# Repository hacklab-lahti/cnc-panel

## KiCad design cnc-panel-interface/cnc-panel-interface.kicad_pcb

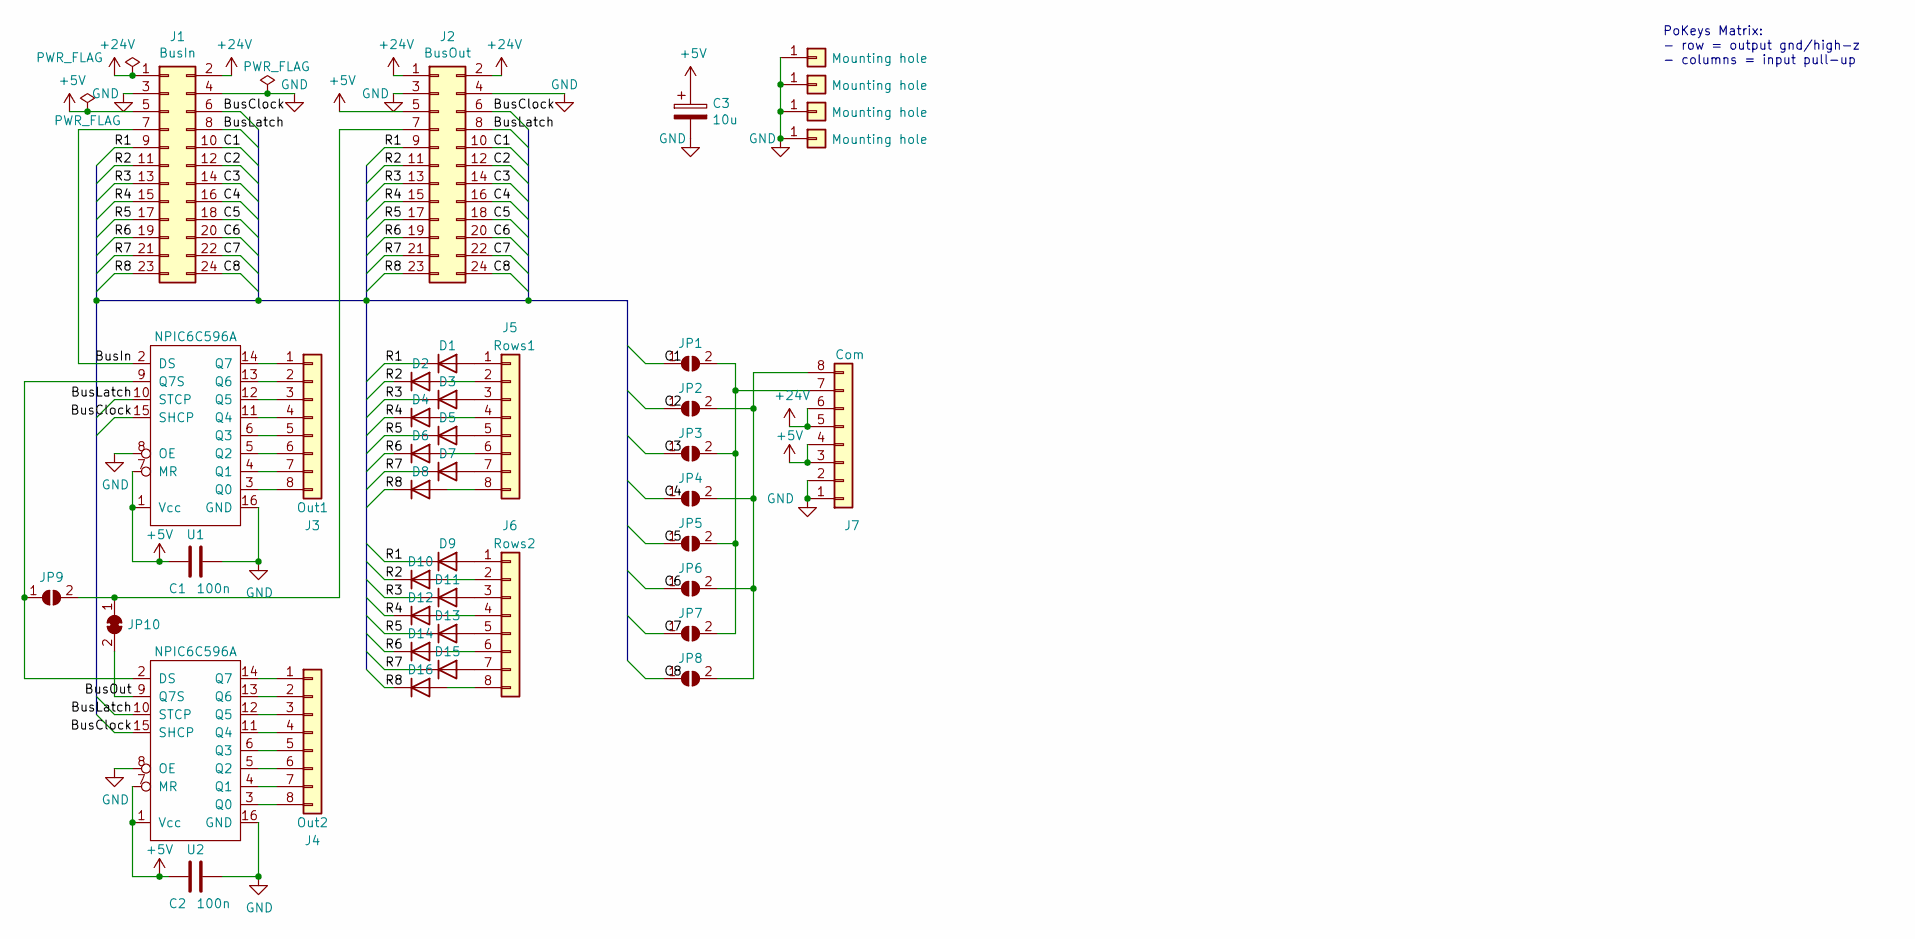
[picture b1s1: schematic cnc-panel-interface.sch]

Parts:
C1, C2: 100n; C_0805_2012Metric_Pad1.15x1.40mm_HandSolder
C3: 10u; CP_Elec_4x4.5
D1, D2, D3, D4, D5, D6, D7, D8, D9, D10, D11, D12, D13, D14, D15, D16: 1N4148; D_SOD-123
J1: BusIn; IDC-Header_2x12_P2.54mm_Vertical_2
J2: BusOut; IDC-Header_2x12_P2.54mm_Vertical_2
J3: Out1; Phoenix1989803
J4: Out2; Phoenix1989803
J5: Rows1; Phoenix1989803
J6: Rows2; Phoenix1989803
J7: Com; Phoenix1989803
J8, J9, J10, J11: Mounting hole; MountingHole_3.2mm_M3_Pad
JP1, JP2, JP3, JP4, JP5, JP6, JP7, JP8, JP9: SolderJumper_2_Open; SolderJumper-2_P1.3mm_Open_RoundedPad1.0x1.5mm
JP10: SolderJumper_2_Bridged; SolderJumper-2_P1.3mm_Bridged_RoundedPad1.0x1.5mm
U1, U2: NPIC6C596A; SOIC-16_3.9x9.9mm_P1.27mm

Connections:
+5V: C1.1, C2.1, C3.1, J1.5, J2.5, J7.3, J7.4, U1.1 (Vcc), U1.7 (MR), U2.1 (Vcc), U2.7 (MR)
+24V: J1.1, J1.2, J2.1, J2.2, J7.5, J7.6
/BusClock: J1.6, J2.6, U1.15 (SHCP), U2.15 (SHCP)
/BusIn: J1.7, U1.2 (DS)
/BusLatch: J1.8, J2.8, U1.10 (STCP), U2.10 (STCP)
/BusOut: JP10.2 (B), U2.9 (Q7S)
/C1: J1.10, J2.10, JP1.1 (A)
/C2: J1.12, J2.12, JP2.1 (A)
/C3: J1.14, J2.14, JP3.1 (A)
/C4: J1.16, J2.16, JP4.1 (A)
/C5: J1.18, J2.18, JP5.1 (A)
/C6: J1.20, J2.20, JP6.1 (A)
/C7: J1.22, J2.22, JP7.1 (A)
/C8: J1.24, J2.24, JP8.1 (A)
/R1: D1.1 (K), D9.1 (K), J1.9, J2.9
/R2: D2.1 (K), D10.1 (K), J1.11, J2.11
/R3: D3.1 (K), D11.1 (K), J1.13, J2.13
/R4: D4.1 (K), D12.1 (K), J1.15, J2.15
/R5: D5.1 (K), D13.1 (K), J1.17, J2.17
/R6: D6.1 (K), D14.1 (K), J1.19, J2.19
/R7: D7.1 (K), D15.1 (K), J1.21, J2.21
/R8: D8.1 (K), D16.1 (K), J1.23, J2.23
GND: C1.2, C2.2, C3.2, J1.3, J1.4, J2.3, J2.4, J7.1, J7.2, J8.1, J9.1, J10.1, J11.1, U1.8 (OE), U1.16 (GND), U2.8 (OE), U2.16 (GND)
unnamed: D1.2 (A), J5.1
unnamed: D2.2 (A), J5.2
unnamed: D3.2 (A), J5.3
unnamed: D4.2 (A), J5.4
unnamed: D5.2 (A), J5.5
unnamed: D6.2 (A), J5.6
unnamed: D7.2 (A), J5.7
unnamed: D8.2 (A), J5.8
unnamed: D9.2 (A), J6.1
unnamed: D10.2 (A), J6.2
unnamed: D11.2 (A), J6.3
unnamed: D12.2 (A), J6.4
unnamed: D13.2 (A), J6.5
unnamed: D14.2 (A), J6.6
unnamed: D15.2 (A), J6.7
unnamed: D16.2 (A), J6.8
unnamed: J2.7, JP9.2 (B), JP10.1 (A)
unnamed: J3.1, U1.14 (Q7)
unnamed: J3.2, U1.13 (Q6)
unnamed: J3.3, U1.12 (Q5)
unnamed: J3.4, U1.11 (Q4)
unnamed: J3.5, U1.6 (Q3)
unnamed: J3.6, U1.5 (Q2)
unnamed: J3.7, U1.4 (Q1)
unnamed: J3.8, U1.3 (Q0)
unnamed: J4.1, U2.14 (Q7)
unnamed: J4.2, U2.13 (Q6)
unnamed: J4.3, U2.12 (Q5)
unnamed: J4.4, U2.11 (Q4)
unnamed: J4.5, U2.6 (Q3)
unnamed: J4.6, U2.5 (Q2)
unnamed: J4.7, U2.4 (Q1)
unnamed: J4.8, U2.3 (Q0)
unnamed: J7.7, JP1.2 (B), JP3.2 (B), JP5.2 (B), JP7.2 (B)
unnamed: J7.8, JP2.2 (B), JP4.2 (B), JP6.2 (B), JP8.2 (B)
unnamed: JP9.1 (A), U1.9 (Q7S), U2.2 (DS)

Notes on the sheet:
PoKeys Matrix: - row = output gnd/high-z - columns = input pull-up

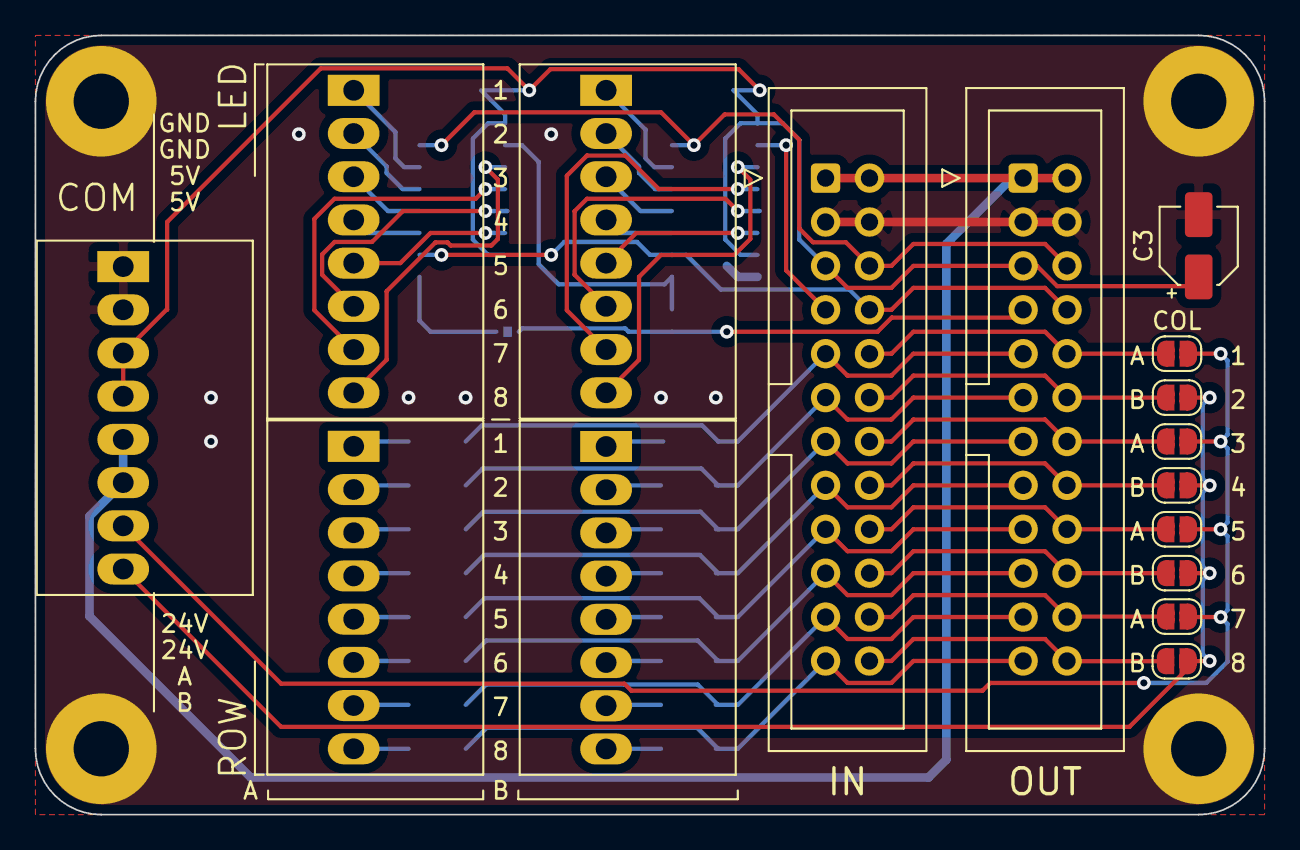
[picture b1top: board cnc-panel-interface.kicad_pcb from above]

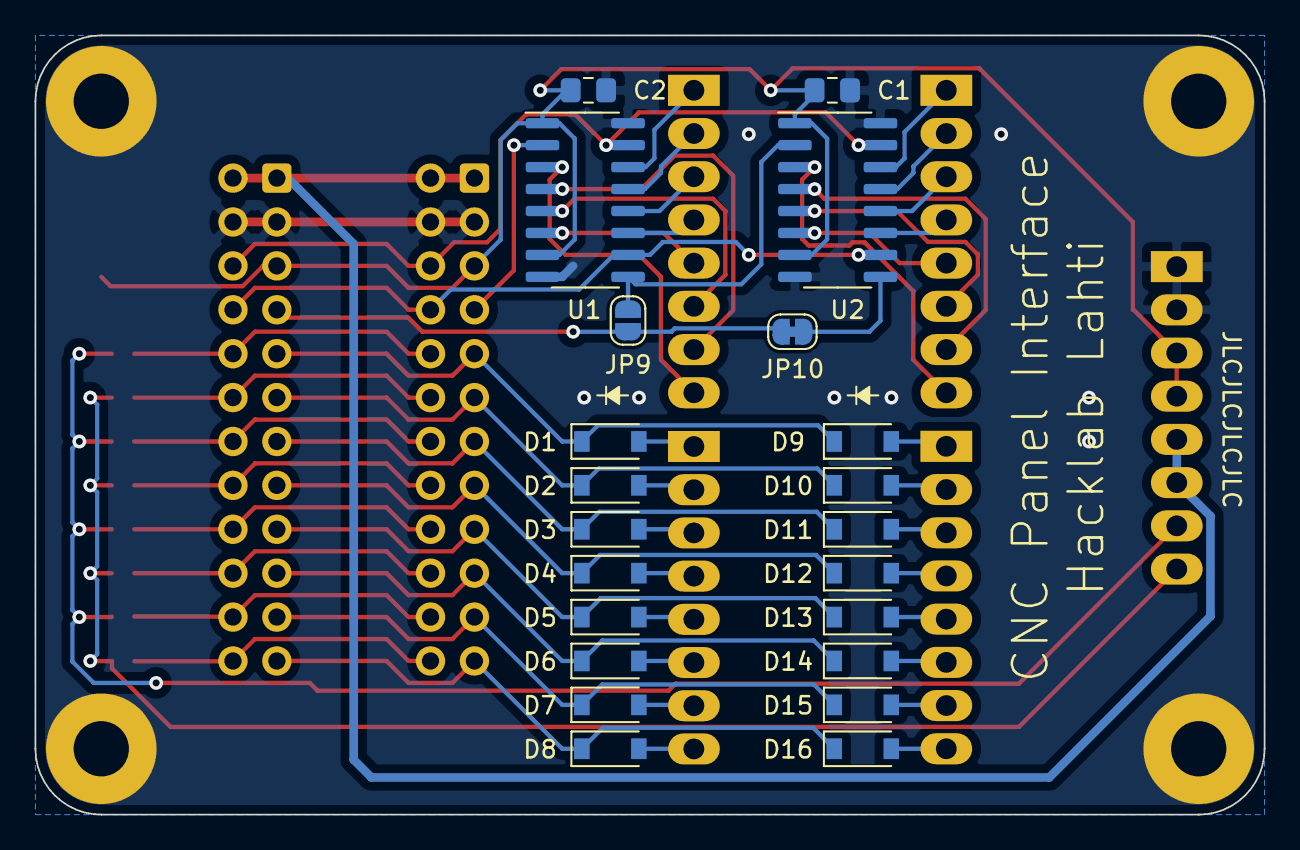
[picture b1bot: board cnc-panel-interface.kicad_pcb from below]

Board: 2 copper layers, 71.1 x 45.1 mm, 42 parts (22 on the bottom side), 59 nets.

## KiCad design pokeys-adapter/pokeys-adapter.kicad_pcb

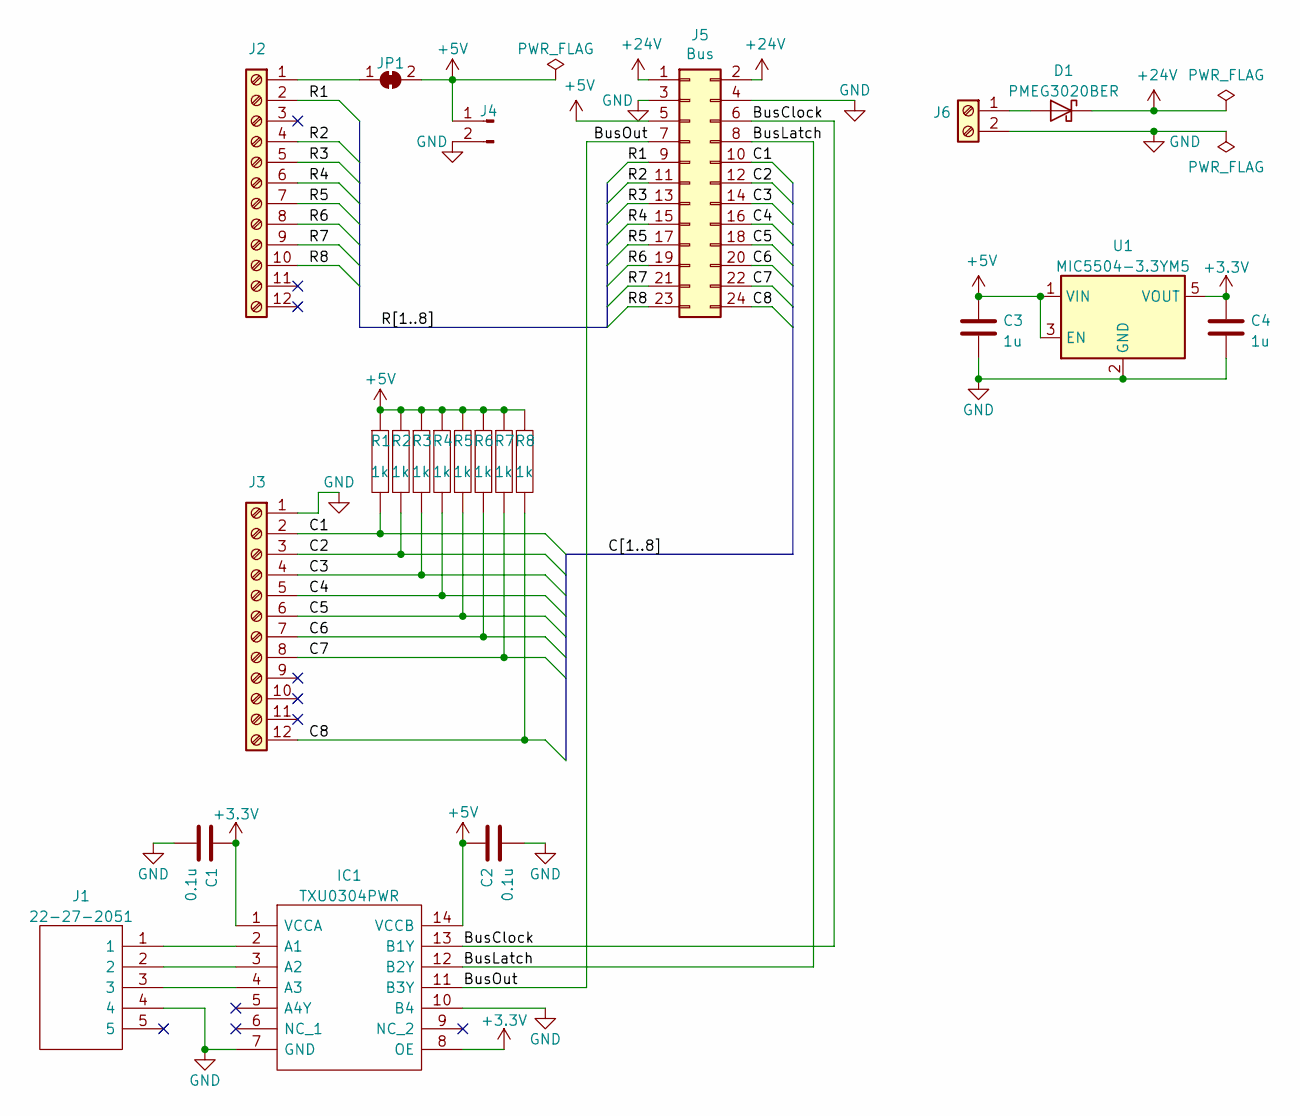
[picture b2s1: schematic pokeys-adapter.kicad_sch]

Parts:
C1, C2: 0.1u; C_0805_2012Metric_Pad1.18x1.45mm_HandSolder
C3, C4: 1u; C_0805_2012Metric_Pad1.18x1.45mm_HandSolder
D1: PMEG3020BER; Nexperia_CFP3_SOD-123W
IC1: TXU0304PWR; TSSOP-14_4.4x5mm_P0.65mm; Mouser Part Number 595-TXU0304PWR
J1: 22-27-2051; HDRV5W64P0X254_1X5_1270X580X1205P; Mouser Part Number 538-22-27-2051
J2, J3: PinHeader_01x12; PinHeader_1x12_P2.54mm_Vertical
J4: Conn_01x02_Male; PinHeader_1x02_P2.54mm_Vertical
J5: Bus; IDC-Header_2x12_P2.54mm_Vertical_2
J6: Screw_Terminal_01x02; TerminalBlock_Phoenix_PT-1,5-2-5.0-H_1x02_P5.00mm_Horizontal
JP1: SolderJumper_2_Bridged; SolderJumper-2_P1.3mm_Bridged2Bar_RoundedPad1.0x1.5mm
R1, R2, R3, R4, R5, R6, R7, R8: 1k; R_0805_2012Metric_Pad1.20x1.40mm_HandSolder
U1: MIC5504-3.3YM5; SOT-23-5

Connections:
+3V3: C1.1, C4.1, IC1.1 (VCCA), IC1.8 (OE), U1.5 (VOUT)
+5V: C2.1, C3.1, IC1.14 (VCCB), J4.1, J5.5, JP1.2 (B), R1.1, R2.1, R3.1, R4.1, R5.1, R6.1, R7.1, R8.1, U1.1 (VIN), U1.3 (EN)
+24V: D1.1 (K), J5.1, J5.2
/BusClock: IC1.13 (B1Y), J5.6
/BusLatch: IC1.12 (B2Y), J5.8
/BusOut: IC1.11 (B3Y), J5.7
/C1: J3.2, J5.10, R1.2
/C2: J3.3, J5.12, R2.2
/C3: J3.4, J5.14, R3.2
/C4: J3.5, J5.16, R4.2
/C5: J3.6, J5.18, R5.2
/C6: J3.7, J5.20, R6.2
/C7: J3.8, J5.22, R7.2
/C8: J3.12, J5.24, R8.2
/R1: J2.2, J5.9
/R2: J2.4, J5.11
/R3: J2.5, J5.13
/R4: J2.6, J5.15
/R5: J2.7, J5.17
/R6: J2.8, J5.19
/R7: J2.9, J5.21
/R8: J2.10, J5.23
GND: C1.2, C2.2, C3.2, C4.2, IC1.7 (GND), IC1.10 (B4), J1.4, J3.1, J4.2, J5.3, J5.4, J6.2, U1.2 (GND)
unnamed: D1.2 (A), J6.1
unnamed: IC1.2 (A1), J1.1
unnamed: IC1.3 (A2), J1.2
unnamed: IC1.4 (A3), J1.3
unnamed: J2.1, JP1.1 (A)

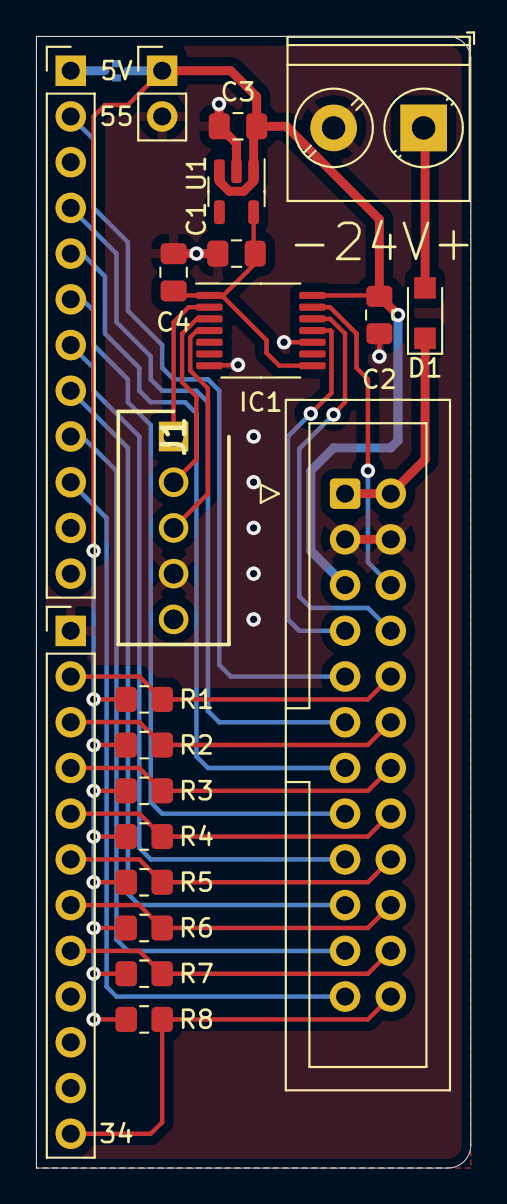
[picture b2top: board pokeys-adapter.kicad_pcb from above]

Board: 2 copper layers, 24.1 x 62.9 mm, 22 parts (1 on the bottom side), 28 nets.

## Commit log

2020-09-26 Minor artistic changes
2020-09-27 Add power flags
2020-10-07 Add 3D printable holder
2022-03-06 Add level shifters and pullups
